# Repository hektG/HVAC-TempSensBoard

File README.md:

# HVAC-TempSensBoard
CSULA HVAC Energy Optimization Lab's temperature and humidity sensor board 
Designed by: Hector G. & Helped By: Jordan D. 
Developed to measure both relative humidity and temperature for enclosures 
Used the Sensirion SHT30-ARP-B sensor to output a analog signal to the header pins and routed that to the DAQ system. 
<br/>
2D View: 

<br/>
3D View:

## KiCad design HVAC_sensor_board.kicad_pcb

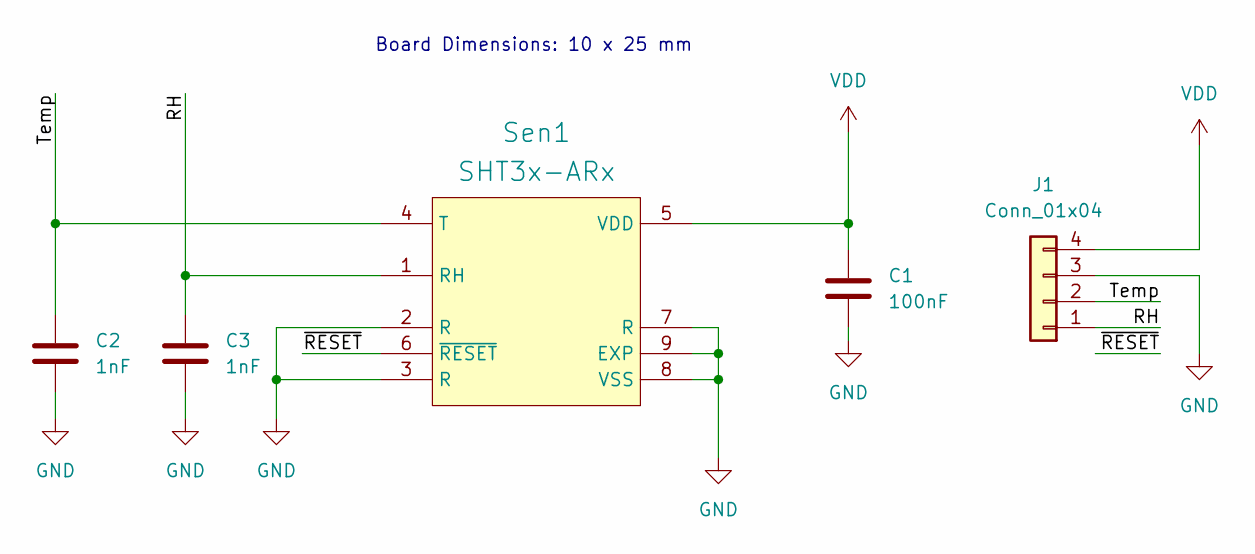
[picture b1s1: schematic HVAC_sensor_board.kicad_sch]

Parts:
C1: 100nF; C_0603_1608Metric
C2, C3: 1nF; C_0603_1608Metric
J1: Conn_01x04; PinHeader_1x04_P2.54mm_Vertical
Sen1: SHT3x-ARx; SHT30

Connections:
/RH: C3.1, J1.1, Sen1.1 (RH)
/Temp: C2.1, J1.2, Sen1.4 (T)
/~RESET: Sen1.6 (~RESET)
GND: C1.2, C2.2, C3.2, J1.3, Sen1.2 (R), Sen1.3 (R), Sen1.7 (R), Sen1.8 (VSS), Sen1.9 (EXP)
VDD: C1.1, J1.4, Sen1.5 (VDD)

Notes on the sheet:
Board Dimensions: 10 x 25 mm

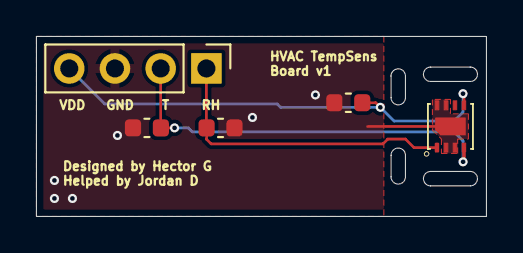
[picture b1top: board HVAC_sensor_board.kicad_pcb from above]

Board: 2 copper layers, 25.0 x 10.0 mm, 5 parts (0 on the bottom side), 4 nets.

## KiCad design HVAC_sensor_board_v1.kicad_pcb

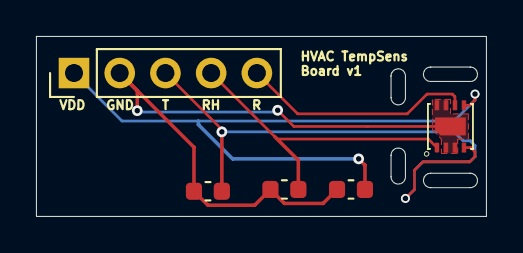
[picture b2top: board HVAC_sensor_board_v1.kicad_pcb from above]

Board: 2 copper layers, 25.0 x 10.0 mm, 5 parts (0 on the bottom side), 5 nets.

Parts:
C1: 100nF; C_0603_1608Metric
C2, C3: 1nF; C_0603_1608Metric
J1: Conn_01x05; PinHeader_1x05_P2.54mm_Vertical
Sen1: SHT3x-ARx; SHT30

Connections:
/RH: C3.1, J1.4, Sen1.1 (RH)
/Temp: C2.1, J1.3, Sen1.4 (T)
/~RESET: J1.5, Sen1.6 (~RESET)
GND: C1.2, C2.2, C3.2, J1.2, Sen1.2 (R), Sen1.3 (R), Sen1.7 (R), Sen1.8 (VSS), Sen1.9 (EXP)
VDD: C1.1, J1.1, Sen1.5 (VDD)
